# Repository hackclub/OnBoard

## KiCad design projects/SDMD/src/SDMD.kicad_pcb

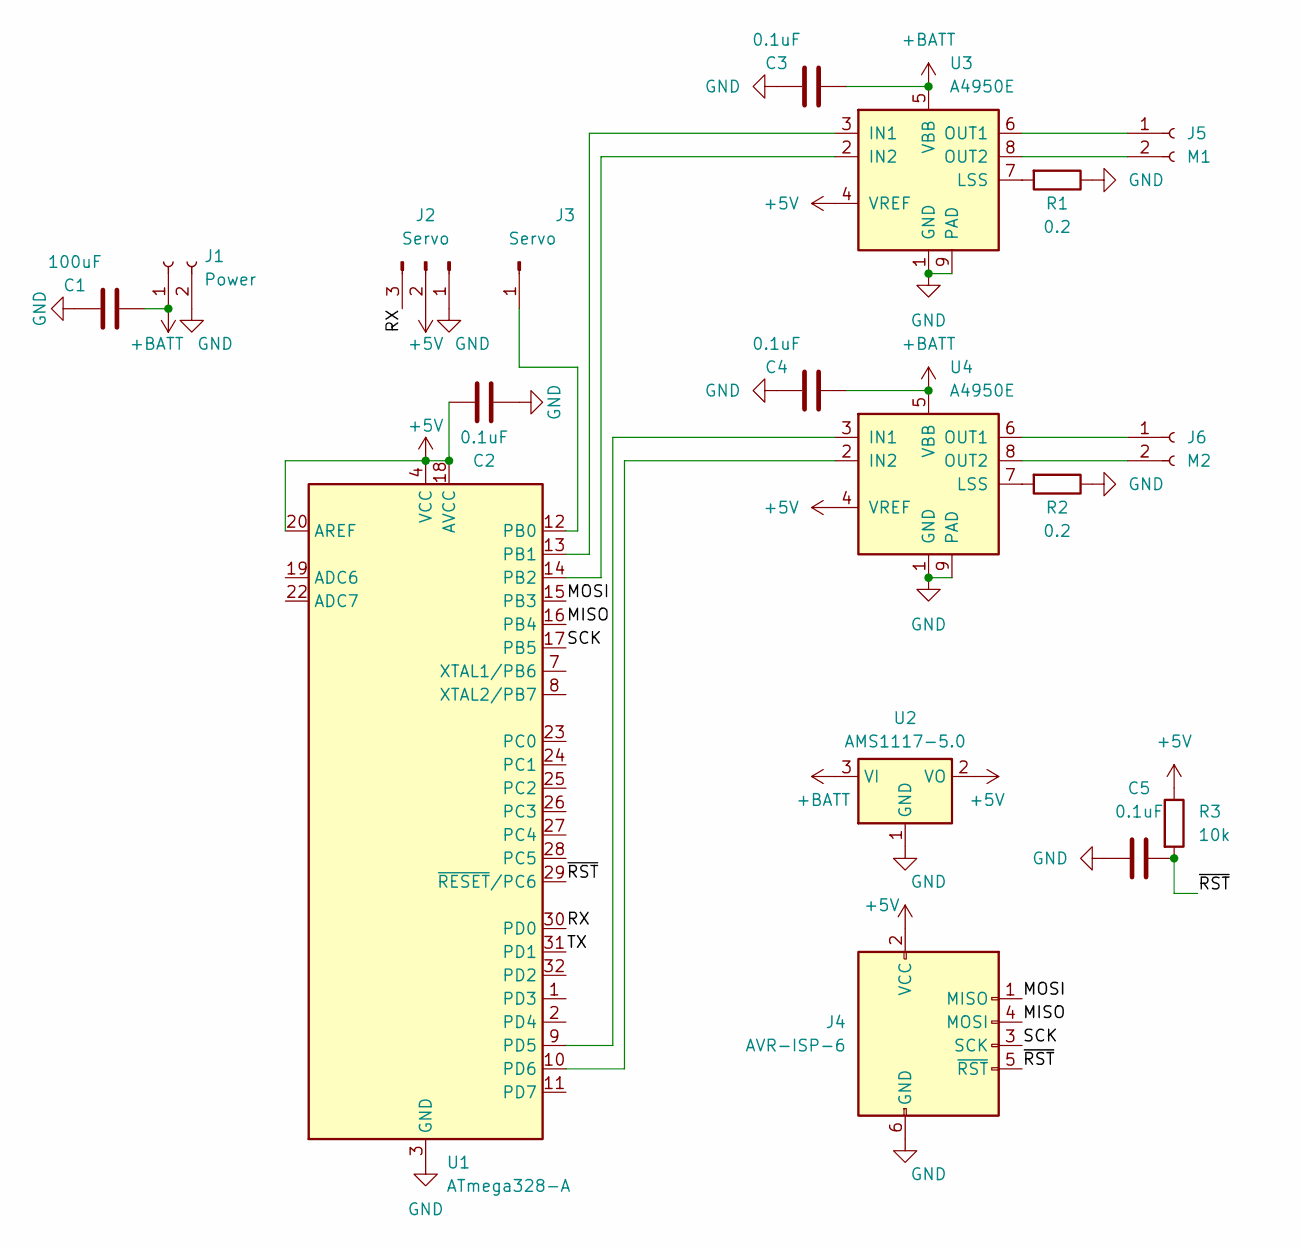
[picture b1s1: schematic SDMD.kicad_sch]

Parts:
C1: 100uF; C_1206_3216Metric
C2, C3, C4, C5: 0.1uF; C_0805_2012Metric
J1: Power; PinSocket_1x02_P2.54mm_Vertical
J2: Servo; PinHeader_1x03_P2.54mm_Vertical
J3: Servo; PinHeader_1x01_P2.54mm_Vertical
J4: AVR-ISP-6; PinHeader_2x03_P2.54mm_Vertical
J5: M1; PinSocket_1x02_P2.54mm_Vertical
J6: M2; PinSocket_1x02_P2.54mm_Vertical
R1, R2: 0.2; R_0805_2012Metric
R3: 10k; R_0805_2012Metric
U1: ATmega328-A; TQFP-32_7x7mm_P0.8mm
U2: AMS1117-5.0; SOT-223-3_TabPin2
U3, U4: A4950E; SOIC-8-1EP_3.9x4.9mm_P1.27mm_EP2.41x3.3mm

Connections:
+5V: C2.2, J2.2, J4.2 (VCC), R3.1, U1.4 (VCC), U1.6 (VCC), U1.18 (AVCC), U1.20 (AREF), U2.2 (VO), U3.4 (VREF), U4.4 (VREF)
+BATT: C1.1, C3.1, C4.1, J1.1, U2.3 (VI), U3.5 (VBB), U4.5 (VBB)
/MISO: J4.4 (MOSI), U1.16 (PB4)
/MOSI: J4.1 (MISO), U1.15 (PB3)
/RX: J2.3, U1.30 (PD0)
/SCK: J4.3 (SCK), U1.17 (PB5)
/TX: U1.31 (PD1)
/~RST: C5.2, J4.5 (~RST), R3.2, U1.29 (~RESET/PC6)
GND: C1.2, C2.1, C3.2, C4.2, C5.1, J1.2, J2.1, J4.6 (GND), R1.1, R2.1, U1.3 (GND), U1.5 (GND), U1.21 (GND), U2.1 (GND), U3.1 (GND), U3.9 (PAD), U4.1 (GND), U4.9 (PAD)
unnamed: J3.1, U1.12 (PB0)
unnamed: J5.1, U3.6 (OUT1)
unnamed: J5.2, U3.8 (OUT2)
unnamed: J6.1, U4.6 (OUT1)
unnamed: J6.2, U4.8 (OUT2)
unnamed: U1.13 (PB1), U3.3 (IN1)
unnamed: U1.14 (PB2), U3.2 (IN2)
unnamed: U1.9 (PD5), U4.3 (IN1)
unnamed: U1.10 (PD6), U4.2 (IN2)
unnamed: R1.2, U3.7 (LSS)
unnamed: R2.2, U4.7 (LSS)

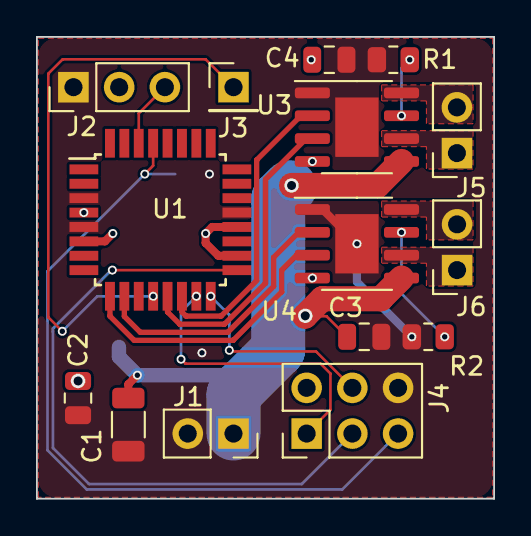
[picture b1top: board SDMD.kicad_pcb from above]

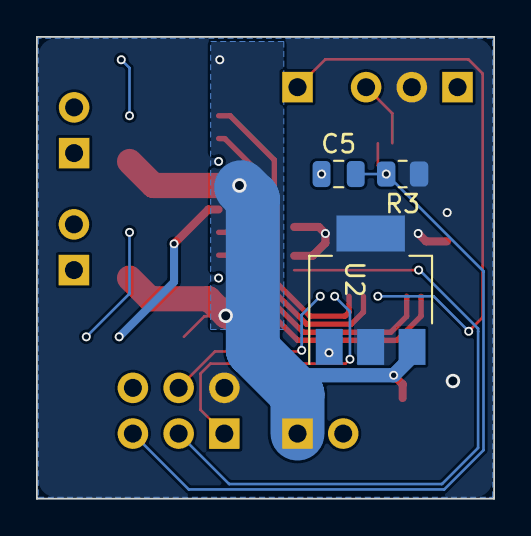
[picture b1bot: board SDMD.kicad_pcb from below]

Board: 2 copper layers, 25.4 x 25.7 mm, 19 parts (3 on the bottom side), 19 nets.

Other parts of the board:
kibuzzard-64FD511C: G***; kibuzzard-64FD511C

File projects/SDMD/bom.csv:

Designator,Footprint,Quantity,Value,LCSC Part #
C1,1206,1,100uF,
"C2, C3, C4, C5",0805,4,0.1uF,
J1,PinSocket_1x02_P2.54mm_Vertical,1,Power,
J2,PinHeader_1x03_P2.54mm_Vertical,1,Servo,
J3,PinHeader_1x01_P2.54mm_Vertical,1,Servo,
J4,PinHeader_2x03_P2.54mm_Vertical,1,AVR-ISP-6,
J5,PinSocket_1x02_P2.54mm_Vertical,1,M1,
J6,PinSocket_1x02_P2.54mm_Vertical,1,M2,
"R1, R2",0805,2,0.2,
R3,0805,1,10k,
U1,TQFP-32_7x7mm_P0.8mm,1,ATmega328-A,
U2,SOT-223-3_TabPin2,1,AMS1117-5.0,
"U3, U4",SOIC-8-1EP_3.9x4.9mm_P1.27mm_EP2.41x3.3mm,2,A4950E,

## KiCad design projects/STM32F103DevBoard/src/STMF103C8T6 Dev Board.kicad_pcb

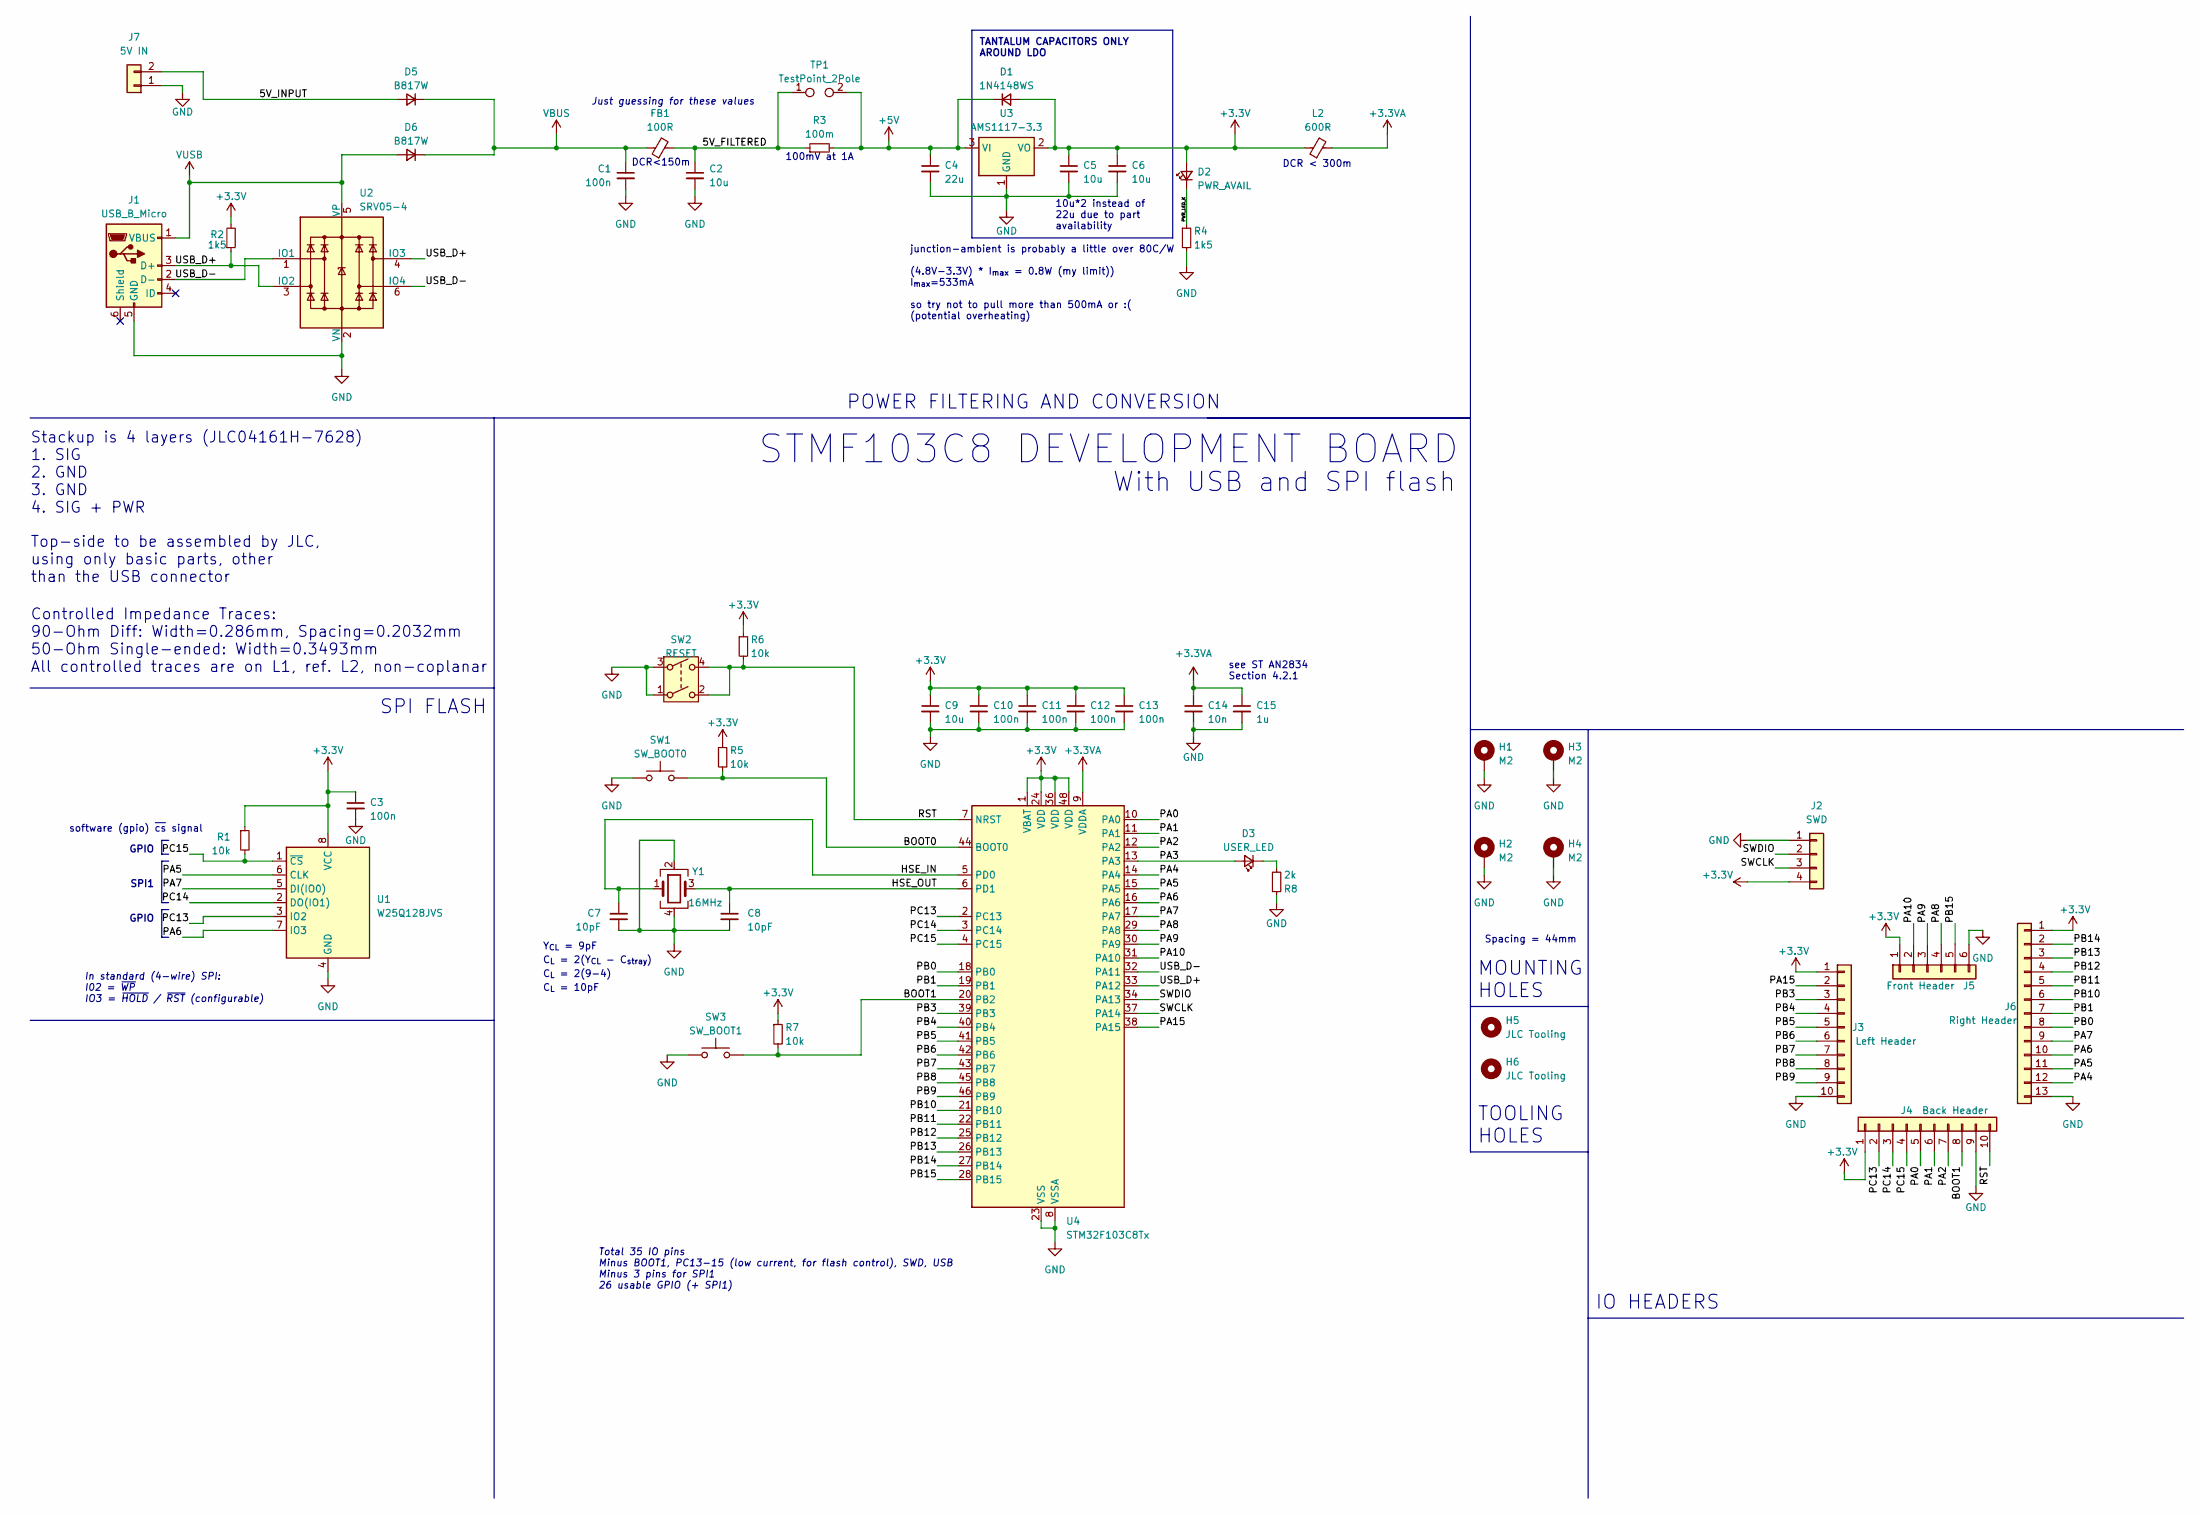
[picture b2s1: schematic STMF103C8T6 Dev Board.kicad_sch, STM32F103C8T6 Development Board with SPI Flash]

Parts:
C1: 100n; C_0603_1608Metric; MPN C14663
C2, C9: 10u; C_0603_1608Metric; MPN C19702
C3, C10, C11, C12, C13: 100n; C_0402_1005Metric; MPN C1525
C4: 22u; C_0603_1608Metric; MPN C59461
C5, C6: 10u; C_1206_3216Metric; MPN C7171
C7, C8: 10pF; C_0402_1005Metric; MPN C32949
C14: 10n; C_0402_1005Metric; MPN C15195
C15: 1u; C_0402_1005Metric; MPN C52923
D1: 1N4148WS; D_SOD-323; MPN C2128
D2: PWR_AVAIL; LED_0603_1608Metric; MPN C2286
D3: USER_LED; LED_0603_1608Metric; MPN C72038
D5, D6: B817W; D_SOD-123; MPN C7420328
FB1: 100R; L_0805_2012Metric_Pad1.05x1.20mm_HandSolder; MPN C1015
H1, H2, H3, H4: M2; MountingHole_2.2mm_M2_Pad
H5, H6: JLC Tooling; JLCPCB Tooling Hole
J1: USB_B_Micro; AMPHENOL_10118194-0001LF; MPN C132562
J2: SWD; PinHeader_1x04_P2.54mm_Vertical
J3: Left Header; PinHeader_1x10_P2.54mm_Vertical
J4: Back Header; PinHeader_1x10_P2.54mm_Vertical
J5: Front Header; PinHeader_1x06_P2.54mm_Vertical
J6: Right Header; PinHeader_1x13_P2.54mm_Vertical
J7: 5V IN; PinHeader_1x02_P2.54mm_Vertical
L2: 600R; L_0805_2012Metric_Pad1.05x1.20mm_HandSolder; MPN C1017
R1, R5, R6, R7: 10k; R_0402_1005Metric; MPN C25744
R2, R4: 1k5; R_0402_1005Metric; MPN C25867
R3: 100m; R_1206_3216Metric_Pad1.30x1.75mm_HandSolder; MPN C25334
R8: 2k; R_0402_1005Metric; MPN C4109
SW1: SW_BOOT0; 3x4x2mm Switch
SW2: RESET; 3x4x2mm Switch
SW3: SW_BOOT1; 3x4x2mm Switch
TP1: TestPoint_2Pole; TestPoint_2Pads_Pitch2.54mm_Drill0.8mm
U1: W25Q128JVS; SOIC-8_5.23x5.23mm_P1.27mm; MPN C97521
U2: SRV05-4; SOT-23-6_Handsoldering; MPN C7420376
U3: AMS1117-3.3; SOT-223-3_TabPin2; MPN C6186
U4: STM32F103C8Tx; LQFP-48_7x7mm_P0.5mm; MPN C8734
Y1: 16MHz; Crystal_SMD_Abracon_ABM8G-4Pin_3.2x2.5mm; MPN C13738

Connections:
+3.3V: C3.1, C5.1, C6.1, C9.1, C10.1, C11.1, C12.1, C13.1, D1.2 (A), D2.2 (A), J2.4, J3.1, J4.1, J5.1, J6.1, L2.1, R1.1, R2.2, R5.1, R6.1, R7.1, U1.8 (VCC), U3.2 (VO), U4.1 (VBAT), U4.24 (VDD), U4.36 (VDD), U4.48 (VDD)
+3.3VA: C14.1, C15.1, L2.2, U4.9 (VDDA)
+5V: C4.1, D1.1 (K), R3.2, TP1.2, U3.3 (VI)
/5V_FILTERED: C2.1, FB1.2, R3.1, TP1.1
/5V_INPUT: D5.2 (A), J7.2
/BOOT0: R5.2, SW1.2, U4.44 (BOOT0)
/BOOT1: J4.8, R7.2, SW3.2, U4.20 (PB2)
/HSE_IN: C7.1, U4.5 (PD0), Y1.1
/HSE_OUT: C8.1, U4.6 (PD1), Y1.3
/PA0: J4.5, U4.10 (PA0)
/PA1: J4.6, U4.11 (PA1)
/PA2: J4.7, U4.12 (PA2)
/PA3: D3.2 (A), U4.13 (PA3)
/PA4: J6.12, U4.14 (PA4)
/PA5: J6.11, U1.6 (CLK), U4.15 (PA5)
/PA6: J6.10, U1.7 (IO3), U4.16 (PA6)
/PA7: J6.9, U1.5 (DI(IO0)), U4.17 (PA7)
/PA8: J5.4, U4.29 (PA8)
/PA9: J5.3, U4.30 (PA9)
/PA10: J5.2, U4.31 (PA10)
/PA15: J3.2, U4.38 (PA15)
/PB0: J6.8, U4.18 (PB0)
/PB1: J6.7, U4.19 (PB1)
/PB3: J3.3, U4.39 (PB3)
/PB4: J3.4, U4.40 (PB4)
/PB5: J3.5, U4.41 (PB5)
/PB6: J3.6, U4.42 (PB6)
/PB7: J3.7, U4.43 (PB7)
/PB8: J3.8, U4.45 (PB8)
/PB9: J3.9, U4.46 (PB9)
/PB10: J6.6, U4.21 (PB10)
/PB11: J6.5, U4.22 (PB11)
/PB12: J6.4, U4.25 (PB12)
/PB13: J6.3, U4.26 (PB13)
/PB14: J6.2, U4.27 (PB14)
/PB15: J5.5, U4.28 (PB15)
/PC13: J4.2, U1.3 (IO2), U4.2 (PC13)
/PC14: J4.3, U1.2 (DO(IO1)), U4.3 (PC14)
/PC15: J4.4, R1.2, U1.1 (~CS), U4.4 (PC15)
/PWR_LED_K: D2.1 (K), R4.1
/RST: J4.10, R6.2, SW2.2, SW2.4, U4.7 (NRST)
/SWCLK: J2.3, U4.37 (PA14)
/SWDIO: J2.2, U4.34 (PA13)
/USB_D+: J1.3 (D+), R2.1, U2.3 (IO2), U2.4 (IO3), U4.33 (PA12)
/USB_D-: J1.2 (D-), U2.1 (IO1), U2.6 (IO4), U4.32 (PA11)
GND: C1.2, C2.2, C3.2, C4.2, C5.2, C6.2, C7.2, C8.2, C9.2, C10.2, C11.2, C12.2, C13.2, C14.2, C15.2, H1.1, H2.1, H3.1, H4.1, J1.5 (GND), J2.1, J3.10, J4.9, J5.6, J6.13, J7.1, R4.2, R8.1, SW1.1, SW2.1, SW2.3, SW3.1, U1.4 (GND), U2.2 (VN), U3.1 (GND), U4.8 (VSSA), U4.23 (VSS), U4.35 (VSS), U4.47 (VSS), Y1.2, Y1.4
unnamed: D3.1 (K), R8.2
VBUS: C1.1, D5.1 (K), D6.1 (K), FB1.1
VUSB: D6.2 (A), J1.1 (VBUS), U2.5 (VP)

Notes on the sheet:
MOUNTING HOLES
DCR<150m
DCR < 300m
Just guessing for these values
Stackup is 4 layers (JLC04161H-7628) 1. SIG 2. GND 3. GND 4. SIG + PWR
Y_{CL} = 9pF
100mV at 1A
GPIO
10u*2 instead of 22u due to part availability
POWER FILTERING AND CONVERSION
C_{L} = 2(9-4)
SPI FLASH
software (gpio) ~{cs} signal
Top-side to be assembled by JLC, using only basic parts, other than the USB connector
junction-ambient is probably a little over 80C/W (4.8V-3.3V) * I_{max} = 0.8W (my limit)) I_{max}=533mA so try not to pull more than 500mA or :( (potential overheating)
TOOLING HOLES
STMF103C8 DEVELOPMENT BOARD
In standard (4-wire) SPI: I02 = ~{WP} IO3 = ~{HOLD} / ~{RST} (configurable)
With USB and SPI flash
C_{L} = 10pF
Total 35 IO pins Minus BOOT1, PC13-15 (low current, for flash control), SWD, USB Minus 3 pins for SPI1 26 usable GPIO (+ SPI1)
Controlled Impedance Traces: 90-Ohm Diff: Width=0.286mm, Spacing=0.2032mm 50-Ohm Single-ended: Width=0.3493mm All controlled traces are on L1, ref. L2, non-coplanar
C_{L} = 2(Y_{CL} - C_{stray})
TANTALUM CAPACITORS ONLY AROUND LDO
IO HEADERS
SPI1
Spacing = 44mm
see ST AN2834 Section 4.2.1

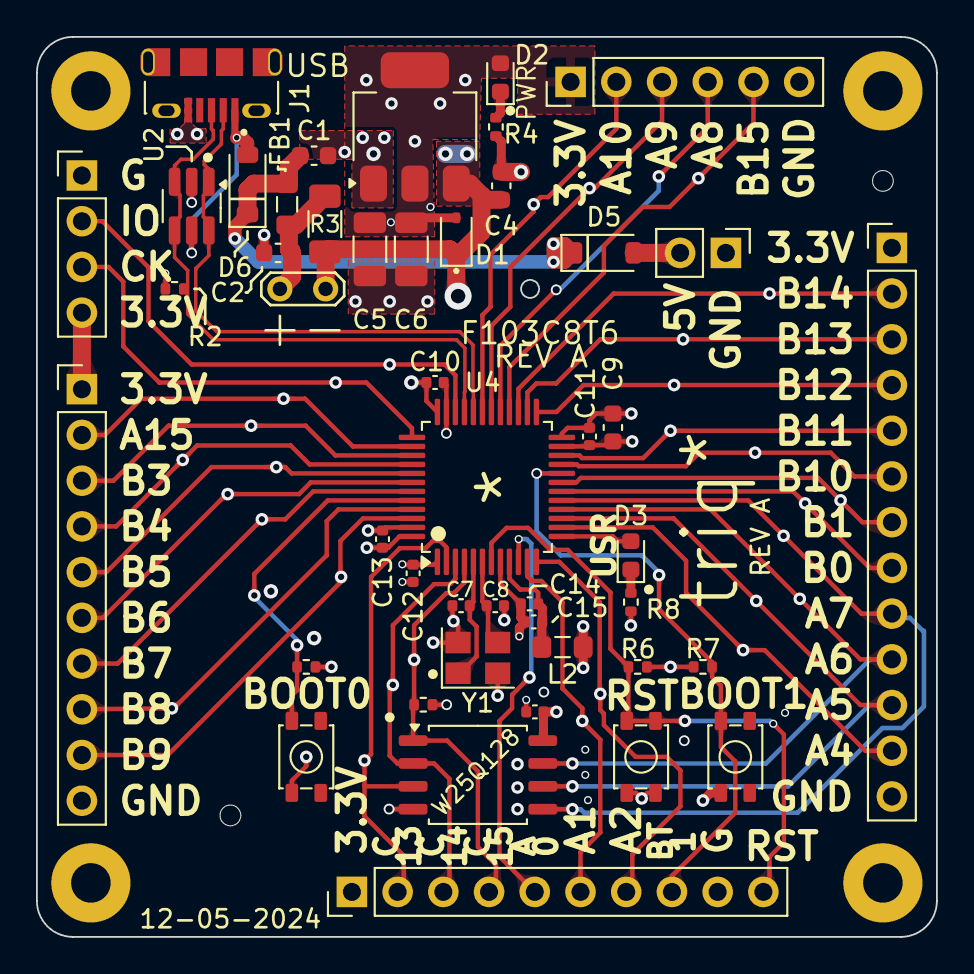
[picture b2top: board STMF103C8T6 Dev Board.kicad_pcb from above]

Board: 4 copper layers, 50.0 x 50.0 mm, 52 parts (0 on the bottom side), 49 nets.

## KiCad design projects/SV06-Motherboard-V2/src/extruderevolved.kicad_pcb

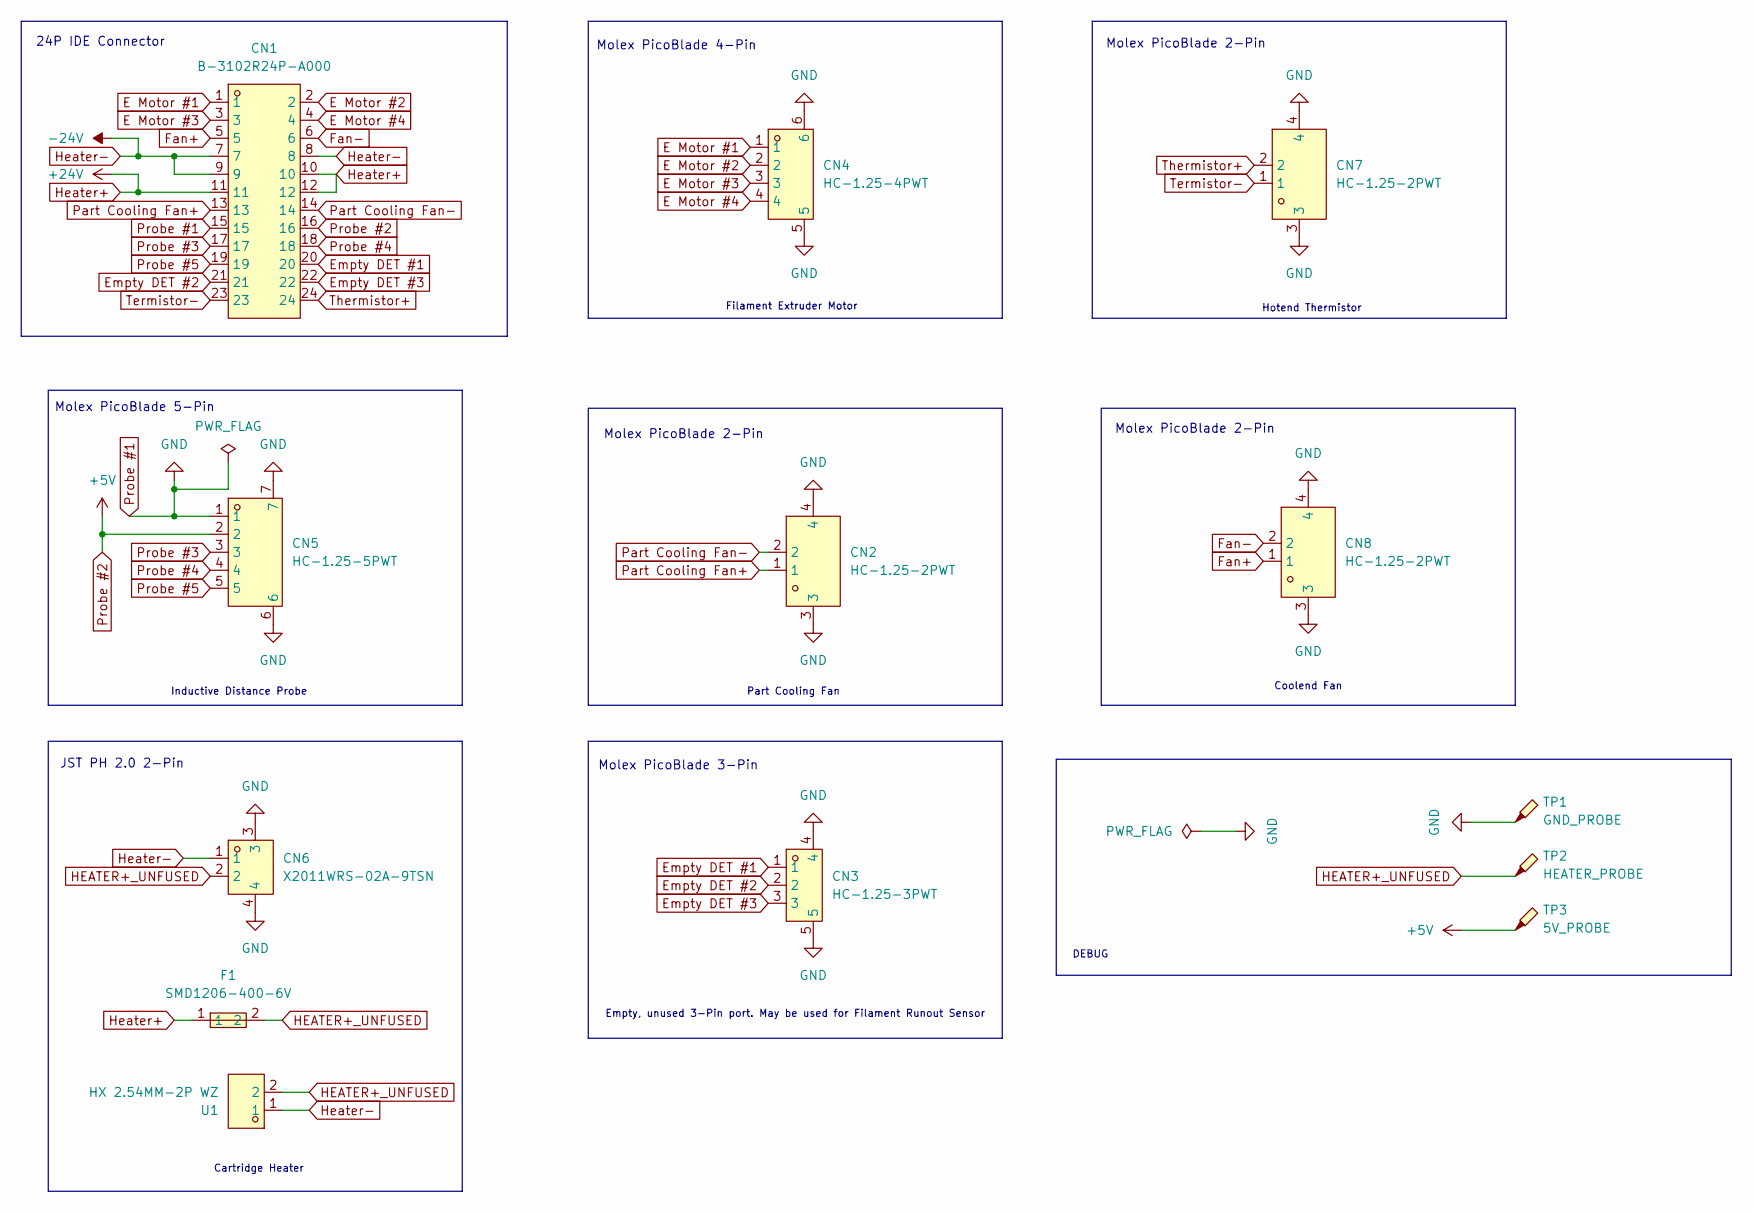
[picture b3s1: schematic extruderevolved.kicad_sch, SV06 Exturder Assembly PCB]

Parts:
CN1: B-3102R24P-A000; IDC-TH_24P-P2.00_B-3102R24P-A000; LCSC Part C383593
CN2, CN7, CN8: HC-1.25-2PWT; CONN-SMD_2P-P1.25-HC-1.25-2PWT; LCSC Part C2845379
CN3: HC-1.25-3PWT; CONN-SMD_HC-1.25-3PWT; LCSC Part C2845380
CN4: HC-1.25-4PWT; CONN-SMD_4P-P1.25-HC-1.25-4PWT; LCSC Part C2845381
CN5: HC-1.25-5PWT; CONN-SMD_5P-P1.25_HCTL_HC-1.25-5PWT; LCSC Part C2845382
CN6: X2011WRS-02A-9TSN; CONN-SMD_2P-P2.00_XKB_X2011WRS-02A-9TSN; LCSC Part C571320
F1: SMD1206-400-6V; F1206; LCSC Part C2760306
TP1: GND_PROBE; TestPoint_THTPad_D2.5mm_Drill1.2mm
TP2: HEATER_PROBE; TestPoint_THTPad_D2.5mm_Drill1.2mm
TP3: 5V_PROBE; TestPoint_THTPad_D2.5mm_Drill1.2mm
U1: HX 2.54MM-2P WZ; CONN-TH_2P-P2.50_HX-2.54MM-2P-WZ; LCSC Part C7543444

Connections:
E Motor #1: CN1.1, CN4.1
E Motor #2: CN1.2, CN4.2
E Motor #3: CN1.3, CN4.3
E Motor #4: CN1.4, CN4.4
Empty DET #1: CN1.20, CN3.1
Empty DET #2: CN1.21, CN3.2
Empty DET #3: CN1.22, CN3.3
Fan+: CN1.5, CN8.1
Fan-: CN1.6, CN8.2
HEATER+_UNFUSED: CN6.2, F1.2, TP2.1, U1.2
Heater+: CN1.10, CN1.11, CN1.12, F1.1
Heater-: CN1.7, CN1.8, CN1.9, CN6.1, U1.1
Part Cooling Fan+: CN1.13, CN2.1
Part Cooling Fan-: CN1.14, CN2.2
Probe #1: CN1.15, CN2.3, CN2.4, CN3.4, CN3.5, CN4.5, CN4.6, CN5.1, CN5.6, CN5.7, CN6.3, CN6.4, CN7.3, CN7.4, CN8.3, CN8.4, TP1.1
Probe #2: CN1.16, CN5.2, TP3.1
Probe #3: CN1.17, CN5.3
Probe #4: CN1.18, CN5.4
Probe #5: CN1.19, CN5.5
Termistor-: CN1.23, CN7.1
Thermistor+: CN1.24, CN7.2

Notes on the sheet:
24P IDE Connector
Molex PicoBlade 5-Pin
Molex PicoBlade 4-Pin
Molex PicoBlade 2-Pin
JST PH 2.0 2-Pin
Inductive Distance Probe
DEBUG
Empty, unused 3-Pin port. May be used for Filament Runout Sensor
Part Cooling Fan
Filament Extruder Motor
Coolend Fan
Molex PicoBlade 3-Pin
Cartridge Heater
Hotend Thermistor

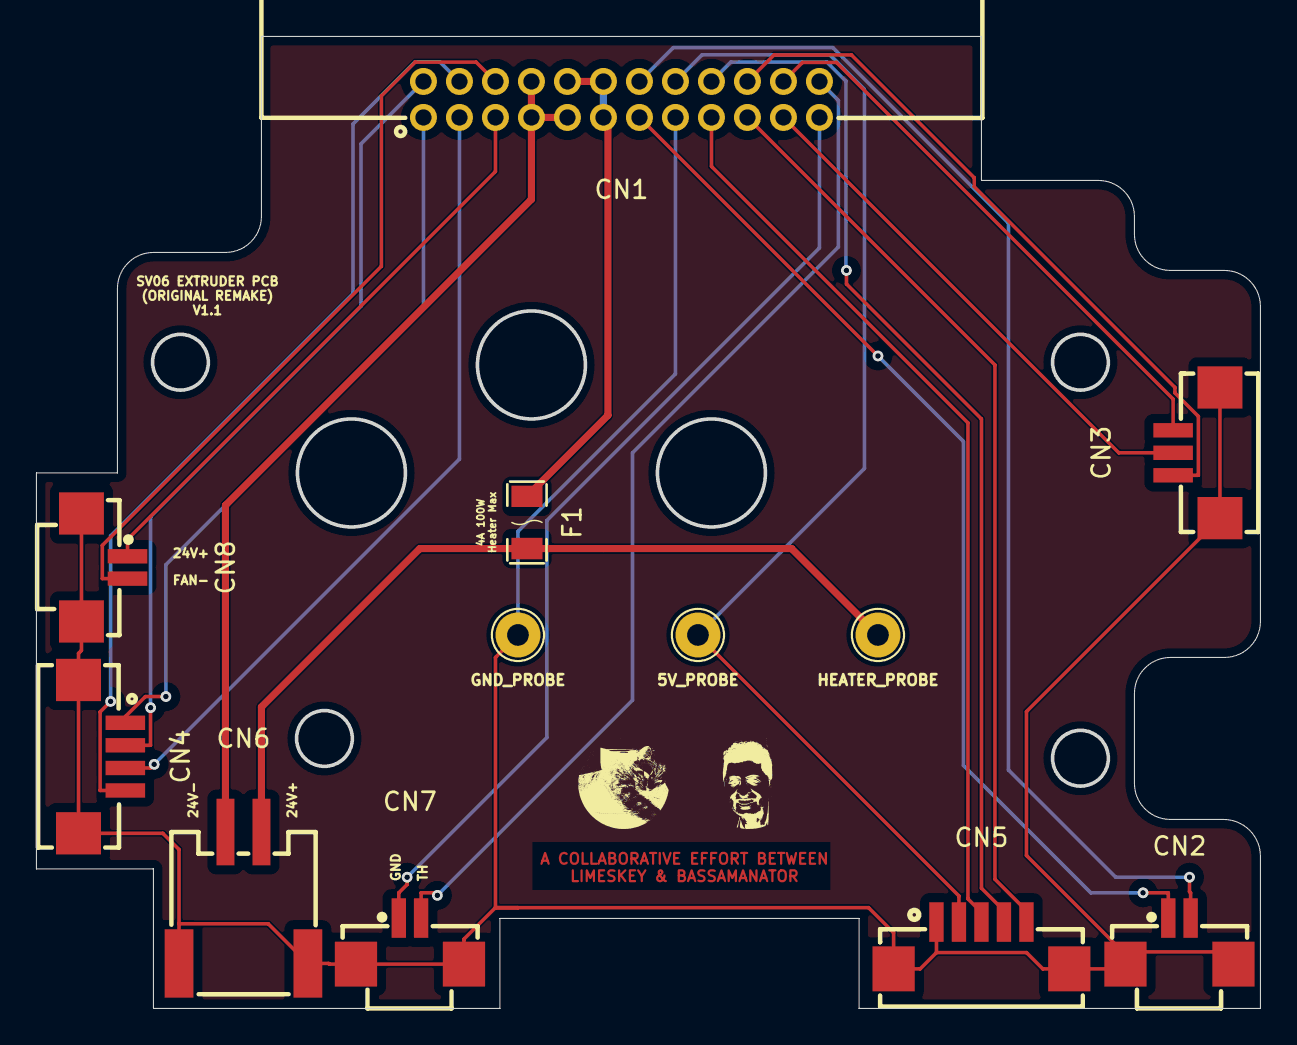
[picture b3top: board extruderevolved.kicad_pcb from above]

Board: 2 copper layers, 68.0 x 54.0 mm, 13 parts (0 on the bottom side), 21 nets.

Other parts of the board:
basamator: LOGO; basa

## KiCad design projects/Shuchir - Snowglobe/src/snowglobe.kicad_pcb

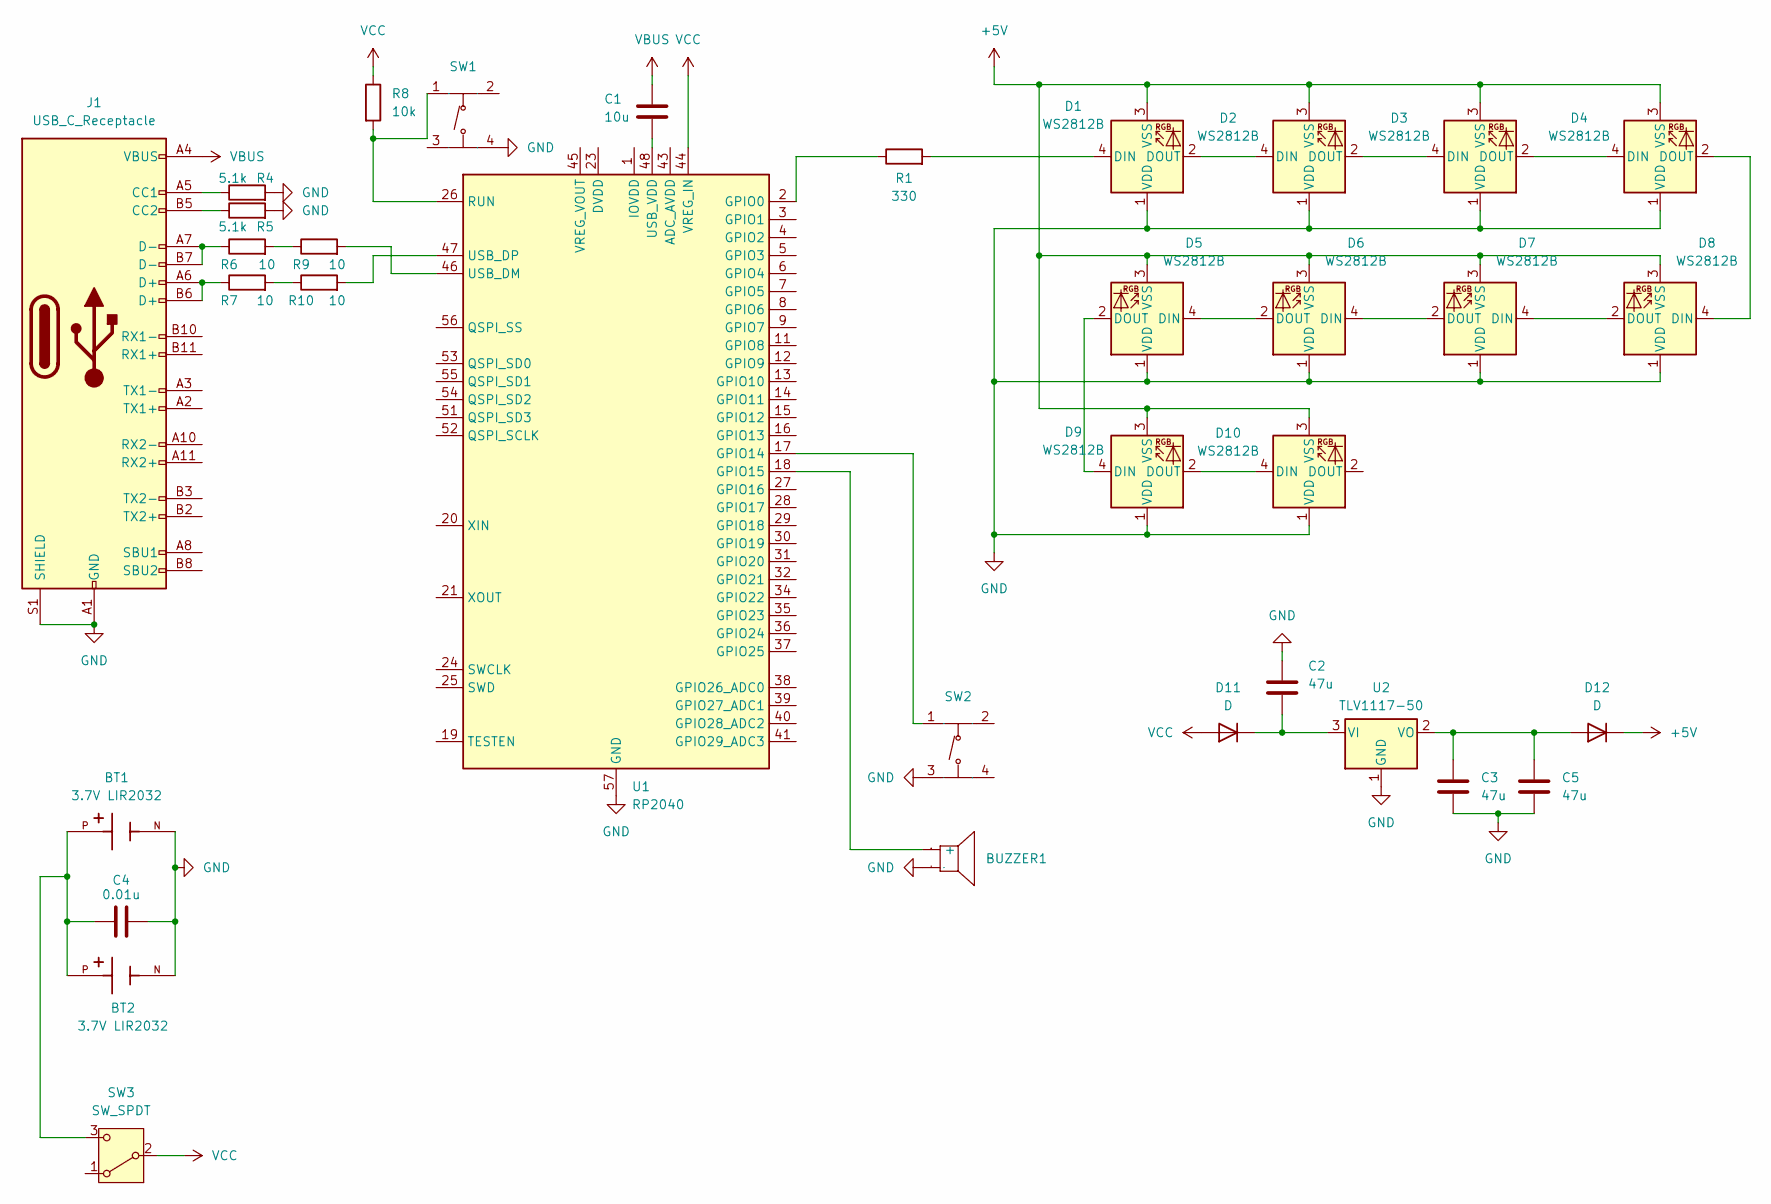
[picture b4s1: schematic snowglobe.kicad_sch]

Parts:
BT1, BT2: 3.7V LIR2032; BAT_CR2032-BS-6-1; PARTREV 2011/2/14
BUZZER1: 4kHz; BUZ-SMD_L12.0-W12.0_FUET-1230
C1: 10u; C_1206_3216Metric
C2, C3, C5: 47u; C_0805_2012Metric
C4: 0.01u; C_1825_4564Metric
D1, D2, D3, D4, D5, D6, D7, D8, D9, D10: WS2812B; LED_WS2812B_PLCC4_5.0x5.0mm_P3.2mm
D11, D12: D; D_SOD-523
J1: USB_C_Receptacle; USB-C_SMD-TYPE-C-31-M-12
R1: 330; R_0603_1608Metric
R4, R5: 5.1k; R_0603_1608Metric
R6, R7, R9, R10: 10; R_0805_2012Metric
R8: 10k; R_0805_2012Metric
SW1, SW2: SW-SMD_4P-L5.1-W5.1-P3.70-LS6.5-TL_H1.5; Manufacturer Part TS-1187A-B-A-B
SW3: SW_SPDT; SW-SMD_K3-1280S-K1
U1: RP2040; QFN-56-1EP_7x7mm_P0.4mm_EP3.2x3.2mm
U2: TLV1117-50; SOT230P700X180-4N

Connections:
+5V: D1.3 (VSS), D2.3 (VSS), D3.3 (VSS), D4.3 (VSS), D5.3 (VSS), D6.3 (VSS), D7.3 (VSS), D8.3 (VSS), D9.3 (VSS), D10.3 (VSS), D12.1 (K)
GND: BT1.N, BT2.N, BUZZER1.2, C2.1, C3.2, C4.2, C5.2, D1.1 (VDD), D2.1 (VDD), D3.1 (VDD), D4.1 (VDD), D5.1 (VDD), D6.1 (VDD), D7.1 (VDD), D8.1 (VDD), D9.1 (VDD), D10.1 (VDD), J1.A1 (GND), J1.A12 (GND), J1.B1 (GND), J1.B12 (GND), J1.S1 (SHIELD), R4.2, R5.2, SW1.4 (D), SW2.3 (C), U1.57 (GND), U2.1 (GND)
unnamed: BUZZER1.1 (+), U1.18 (GPIO15)
unnamed: D1.4 (DIN), R1.2
unnamed: D1.2 (DOUT), D2.4 (DIN)
unnamed: D2.2 (DOUT), D3.4 (DIN)
unnamed: D3.2 (DOUT), D4.4 (DIN)
unnamed: D4.2 (DOUT), D8.4 (DIN)
unnamed: D5.4 (DIN), D6.2 (DOUT)
unnamed: D5.2 (DOUT), D9.4 (DIN)
unnamed: D6.4 (DIN), D7.2 (DOUT)
unnamed: D7.4 (DIN), D8.2 (DOUT)
unnamed: D9.2 (DOUT), D10.4 (DIN)
unnamed: C2.2, D11.1 (K), U2.3 (VI)
unnamed: C3.1, C5.1, D12.2 (A), U2.2 (VO)
unnamed: J1.A5 (CC1), R4.1
unnamed: J1.B5 (CC2), R5.1
unnamed: J1.A6 (D+), J1.B6 (D+), R7.1
unnamed: J1.A7 (D-), J1.B7 (D-), R6.1
unnamed: R6.2, R9.1
unnamed: R7.2, R10.1
unnamed: R8.2, SW1.1 (A), U1.26 (RUN)
unnamed: SW2.1 (A), U1.17 (GPIO14)
unnamed: BT1.P, BT2.P, C4.1, SW3.3 (C)
unnamed: U1.23 (DVDD), U1.50 (DVDD)
unnamed: R1.1, U1.2 (GPIO0)
unnamed: U1.1 (IOVDD), U1.10 (IOVDD), U1.22 (IOVDD), U1.33 (IOVDD), U1.42 (IOVDD), U1.49 (IOVDD)
unnamed: R9.2, U1.46 (USB_DM)
unnamed: R10.2, U1.47 (USB_DP)
unnamed: C1.2, U1.48 (USB_VDD)
VBUS: C1.1, J1.A4 (VBUS), J1.A9 (VBUS), J1.B4 (VBUS), J1.B9 (VBUS)
VCC: D11.2 (A), R8.1, SW3.2 (B), U1.44 (VREG_IN)

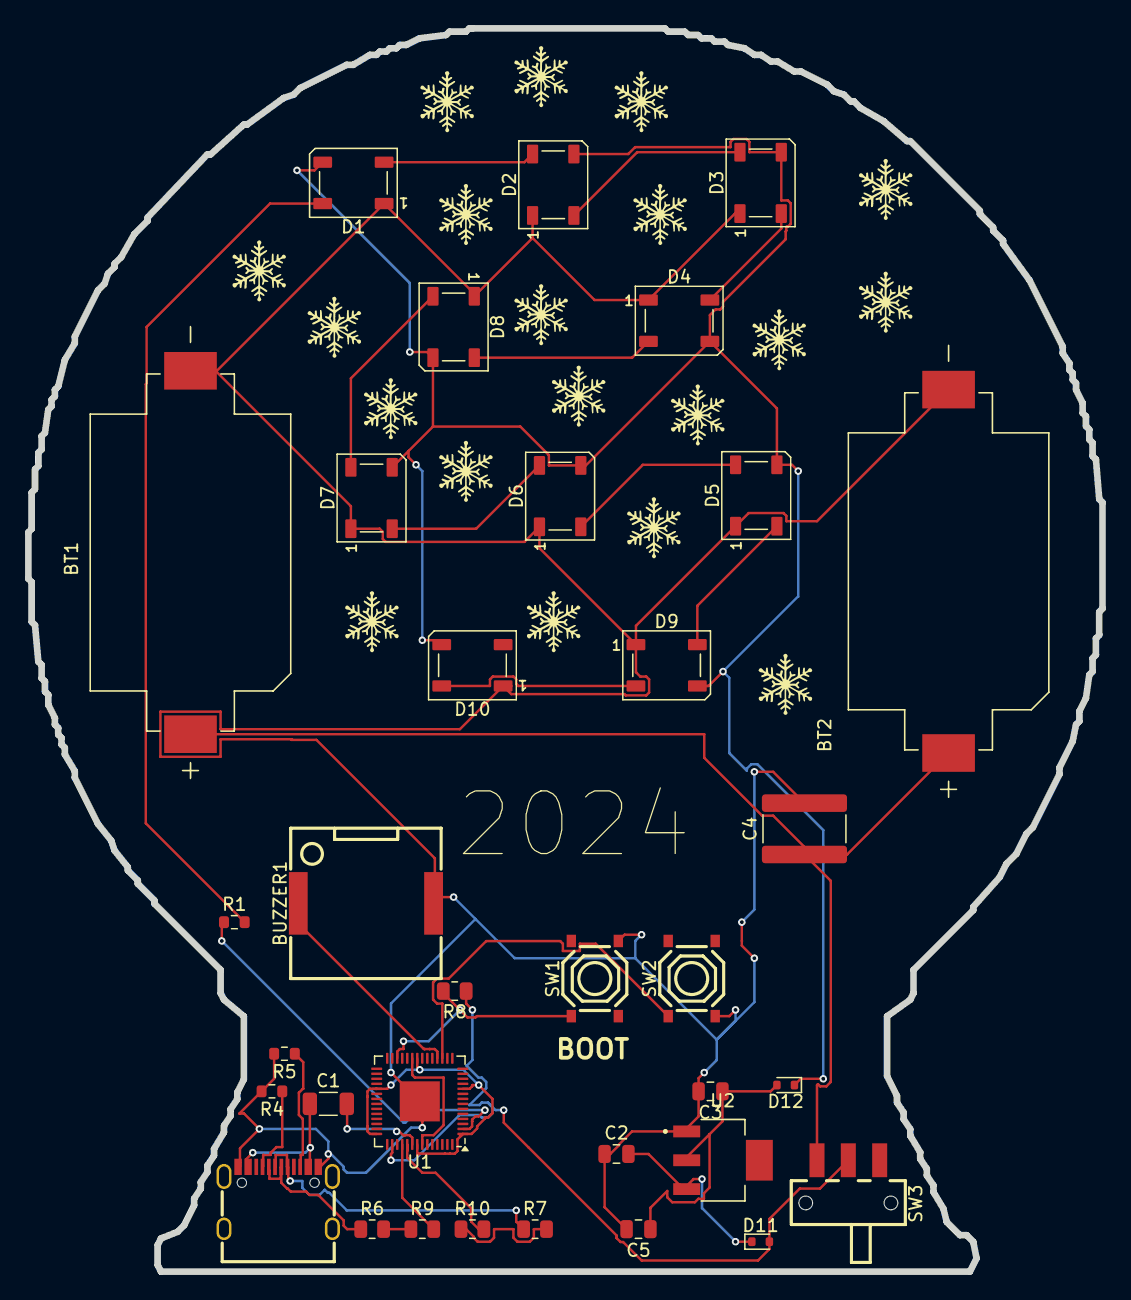
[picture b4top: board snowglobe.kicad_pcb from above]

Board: 2 copper layers, 85.7 x 99.2 mm, 34 parts (0 on the bottom side), 32 nets.

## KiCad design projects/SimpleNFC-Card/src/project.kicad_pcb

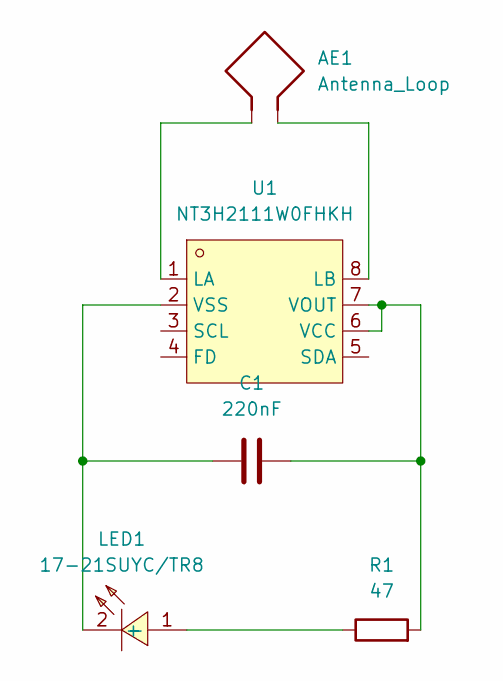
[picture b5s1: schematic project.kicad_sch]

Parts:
AE1: Antenna_Loop; antenna-nfc
C1: 220nF; C_0603_1608Metric; LCSC C21120
LED1: 17-21SUYC/TR8; LED0805-R-RD; LCSC Part C2296
R1: 47; R_0603_1608Metric; LCSC C23182
U1: NT3H2111W0FHKH; XQFN-8_L1.6-W1.6-P0.50-BL_NT3H2111W0FHKH; LCSC Part C710403

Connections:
unnamed: LED1.1 (+), R1.1
unnamed: C1.1, LED1.2 (-), U1.2 (VSS)
unnamed: AE1.1, U1.1 (LA)
unnamed: AE1.2, U1.8 (LB)
unnamed: C1.2, R1.2, U1.6 (VCC), U1.7 (VOUT)

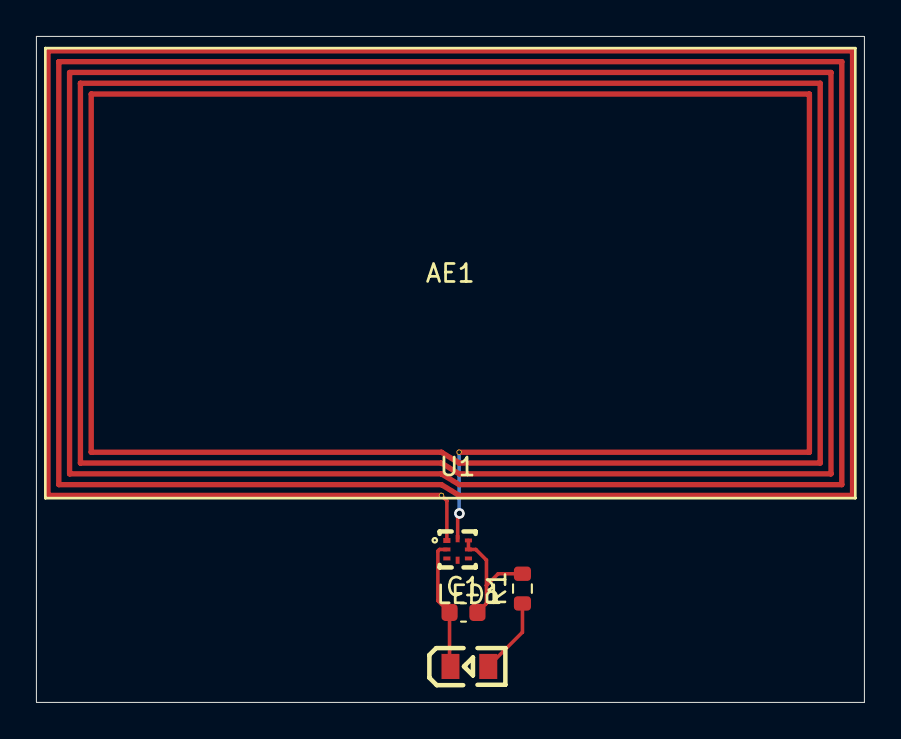
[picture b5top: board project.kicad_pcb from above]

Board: 2 copper layers, 46.0 x 37.0 mm, 5 parts (0 on the bottom side), 5 nets.
